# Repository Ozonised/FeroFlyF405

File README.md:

# FeroFlyF405

FeroFlyF405 is an opensource flight controller based on STM32F405 and runs the open source flight controller firmware, [INAV](https://github.com/iNavFlight/inav).

FeroFlyF405 is designed to be an open hardware platform that enthusiasts and developers can study, modify, build, and use in their own projects.

For those interested in the design process, watch the [YouTube](https://youtu.be/mWAzVRxgooY) video.

## Features

* **Microcontroller:** STM32F405
* **IMU:** LSM6DSL 6-axis accelerometer and gyroscope
* **Barometer:** DPS368
* **Firmware:** INAV
* **Motor outputs:** 12 timer-based output channels
* **CAN bus:** For compatible peripherals
* **I2C:** External sensor and peripheral connectivity
* **UARTs:** 3 serial ports
* **PINIO:** 2 programmable GPIO outputs
* **Current sensing:** Dedicated input for an external current sensor

## Sponsor

A special thanks to **[NextPCB](https://www.nextpcb.com/?code=ozonised)** for sponsoring the FeroFlyF405 project and supporting the development of this open-source flight controller.

Their support helped bring the custom PCB design from the screen to the physical board.

Get high quality PCBs for your project at an affordable rate from **[NextPCB](https://www.nextpcb.com/)**.

## Download
Grab the gerbers and kicad file for the latest stable version from the **[release](https://github.com/Ozonised/FeroFlyF405/releases)** tab.

## Connectivity

| Interface      | Quantity | Purpose                                             |
| -------------- | -------: | --------------------------------------------------- |
| Motor outputs  |       12 | ESCs and other compatible timer-based outputs       |
| CAN bus        |        1 | Compatible CAN peripherals                          |
| I2C            |        1 | External sensors and peripherals                    |
| UART           |        3 | Receivers, GPS, telemetry, and other serial devices |
| PINIO          |        2 | User-configurable GPIO outputs                      |
| Current sensor |        1 | External current-sensing module                     |

> **Note:** Motor output capabilities depend on timer allocation, DMA availability, and firmware configuration. Not all outputs necessarily support every ESC protocol.

## Connectors and Pinout

FeroFlyF405 follows the **Pixhawk connector and pinout standard** for its applicable peripheral interfaces and uses **JST-GH series connectors**.

The PINIO and current-sensor connectors are exceptions to this convention.

## Firmware

FeroFlyF405 runs [INAV](https://github.com/iNavFlight/inav), an open-source flight control firmware for multirotor, fixed-wing, and other UAV platforms.

FeroFlyF405 uses a board-specific INAV target to configure its MCU pins, sensors, timers, communication interfaces, and other hardware resources.

Useful links:
* [FeroFlyF405 Target & Binary](https://github.com/Ozonised/FeroFlyF405-INAV-files)
* [INAV source code](https://github.com/iNavFlight/inav)
* [INAV documentation](https://inavflight.github.io/)

## 3D-Printed Enclosure

The FeroFlyF405 enclosure consists of three 3D-printable parts:

* **Enclosure Top** (`FeroFlyF405 Enclosure-Top.stl`) — Upper section of the enclosure.
* **Enclosure Bottom** (`FeroFlyF405 Enclosure-Bottom.stl`) — Lower section of the enclosure.
* **LED Cap** (`FeroFlyF405 Enclosure-Led Cap.stl`) — Cover for the status and power LEDs, designed to be printed using translucent filament to allow the LED light to pass through.

### Printing Recommendations

* **Top and Bottom:** PETG filament is recommended for durability and heat resistance.
* **LED Cap:** Use translucent filament for better LED visibility.
* **Fasteners:** The enclosure uses M3 screws and threaded inserts.

The STL files are provided so you can print and assemble the enclosure yourself.

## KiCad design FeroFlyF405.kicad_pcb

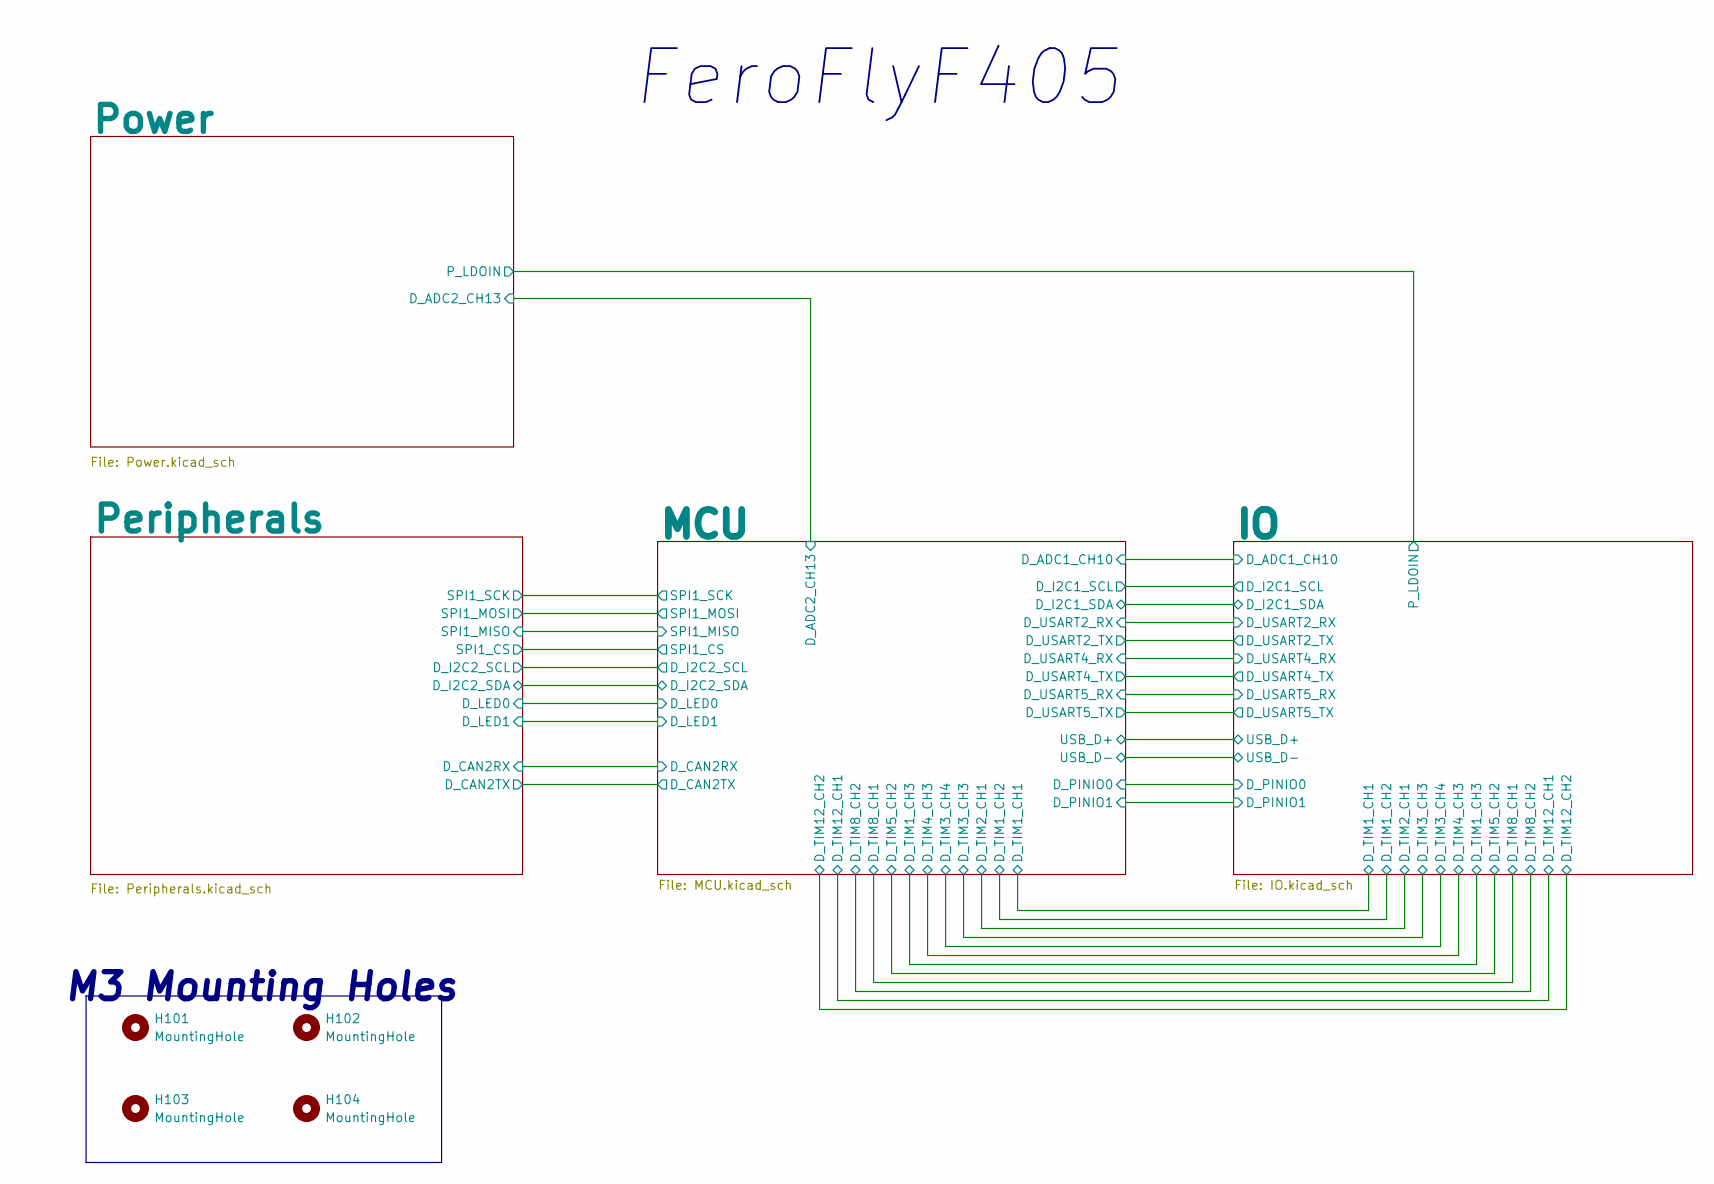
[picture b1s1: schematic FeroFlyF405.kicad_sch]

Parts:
H101, H102, H103, H104: MountingHole; MountingHole_3.2mm_M3

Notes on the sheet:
M3 Mounting Holes
FeroFlyF405

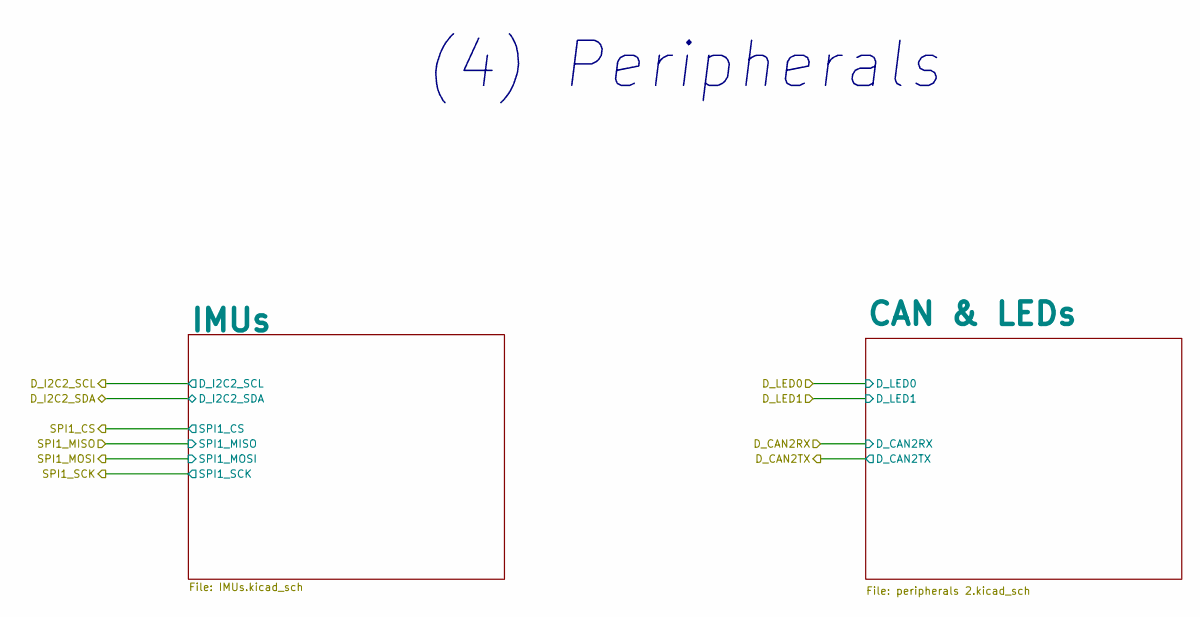
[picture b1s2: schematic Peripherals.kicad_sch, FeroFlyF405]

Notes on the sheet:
(4) Peripherals

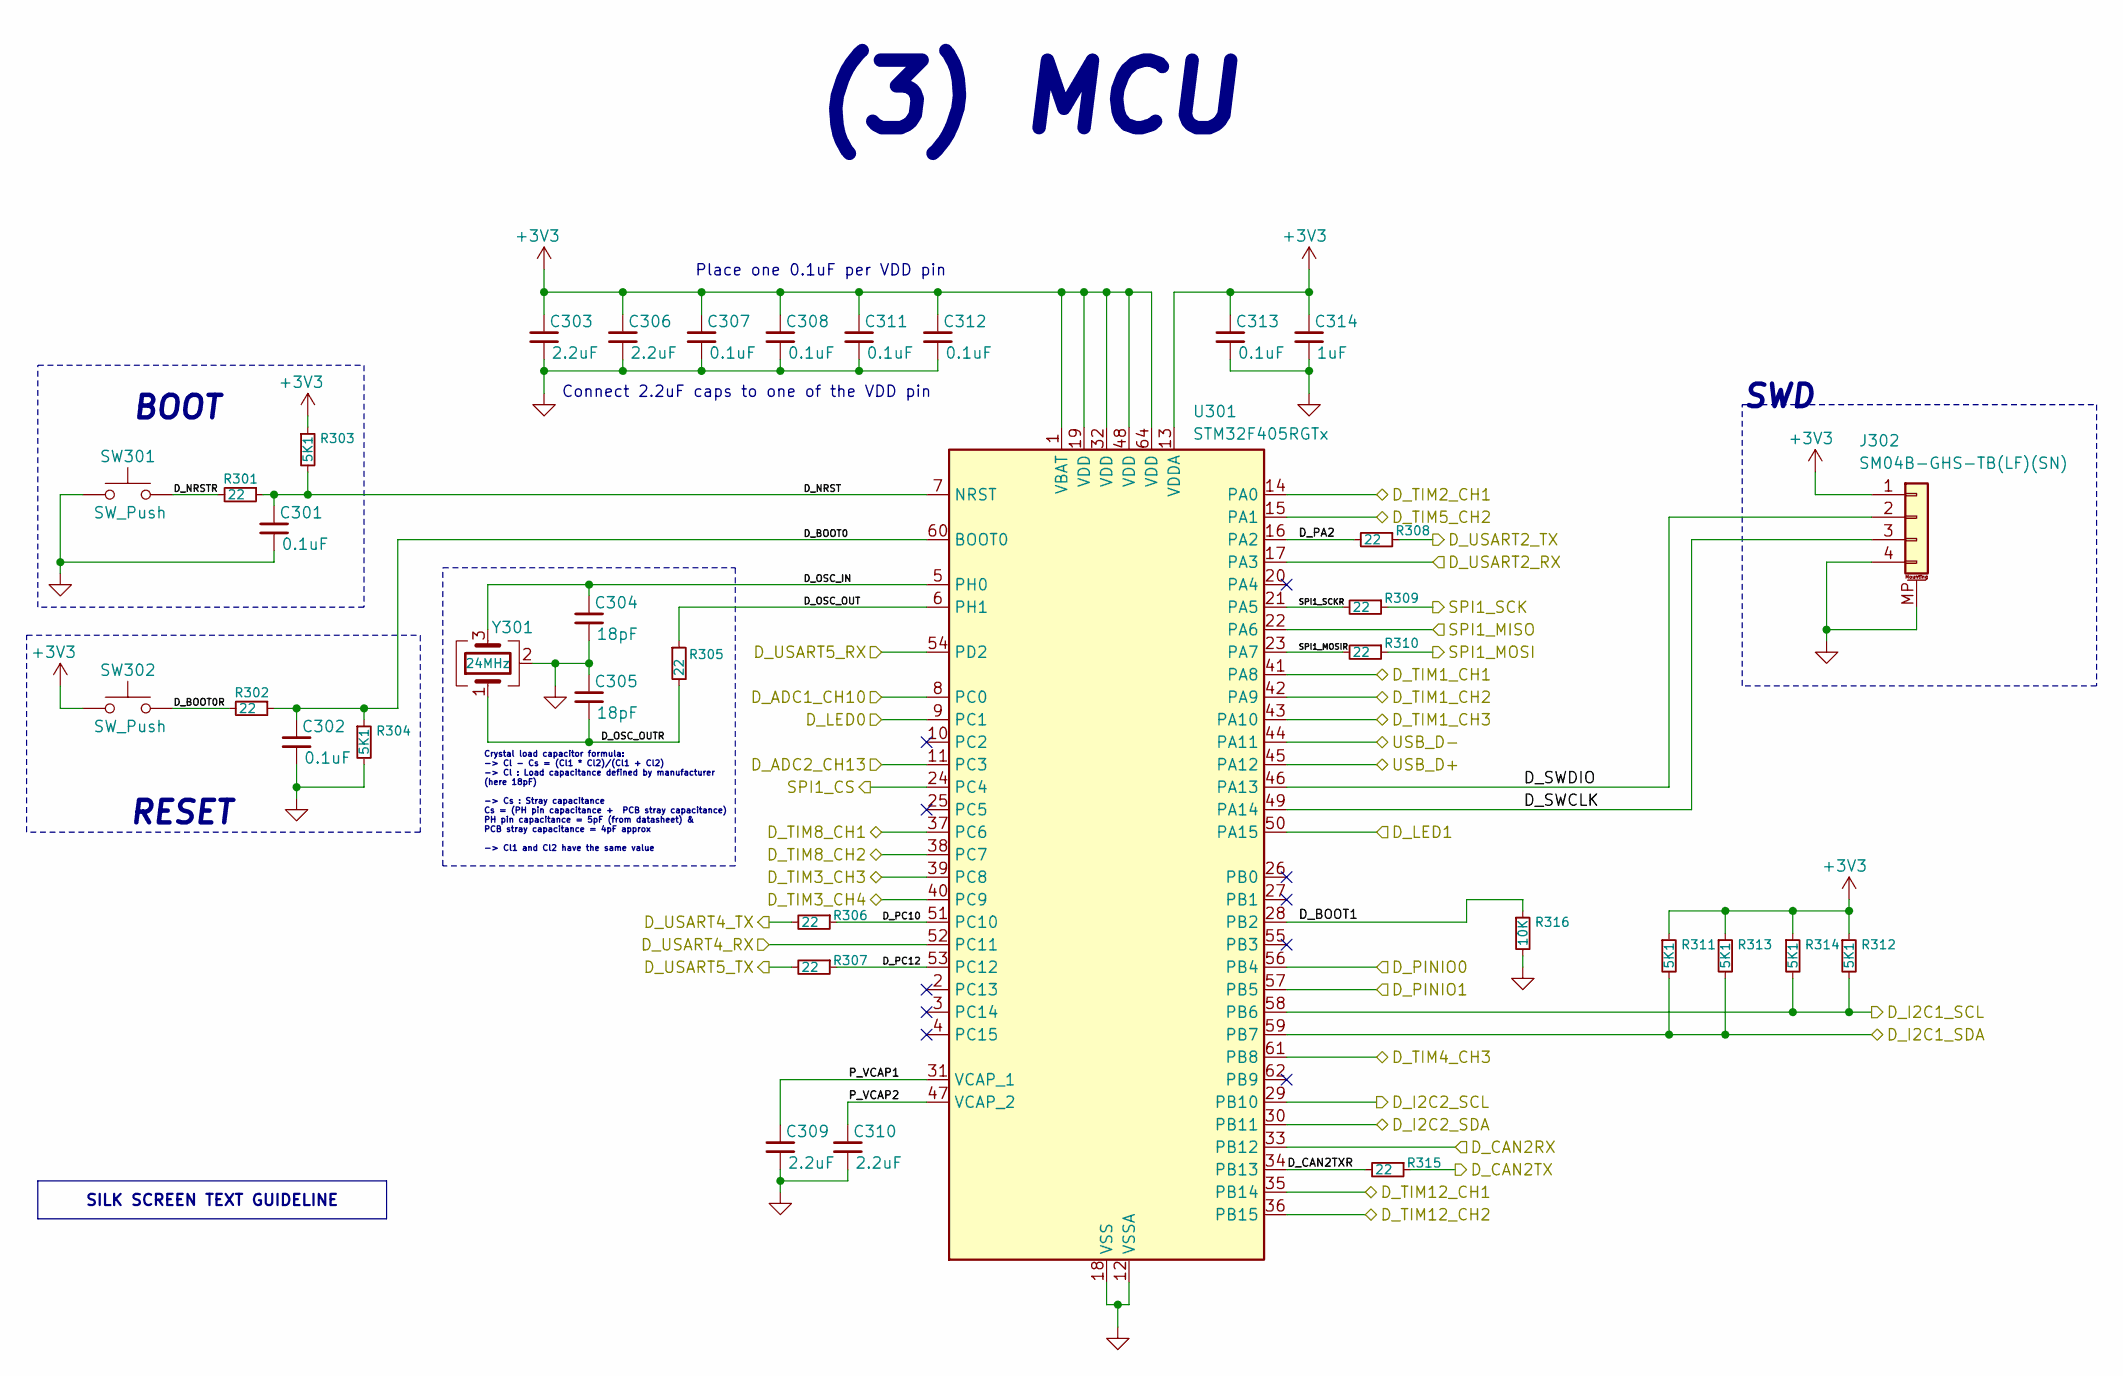
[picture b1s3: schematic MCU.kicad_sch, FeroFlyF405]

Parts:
C301, C302, C307, C308, C311, C312, C313: 0.1uF; C_0603_1608Metric_Pad1.08x0.95mm_HandSolder; MPN C1608X5R1H104K080AA
C303, C306, C309, C310: 2.2uF; C_0805_2012Metric_Pad1.18x1.45mm_HandSolder; MPN GCM21BR71C225KA64L
C304, C305: 18pF; C_0603_1608Metric_Pad1.08x0.95mm_HandSolder; MPN 06035A180JAT4A
C314: 1uF; C_0603_1608Metric_Pad1.08x0.95mm_HandSolder; MPN C1608X7R1V105K080AC
J302: SM04B-GHS-TB(LF)(SN); JST_GH_SM04B-GHS-TB_1x04-1MP_P1.25mm_Horizontal; MPN SM04B-GHS-TB(LF)(SN)
R301, R302, R305, R306, R307, R308, R309, R310, R315: 22; C_0603_1608Metric_Pad1.08x0.95mm_HandSolder; MPN CR0603-FX-22R0ELF
R303, R304, R311, R312, R313, R314: 5K1; R_0603_1608Metric_Pad0.98x0.95mm_HandSolder; MPN CR0603-FX-5101ELF
R316: 10K; R_0603_1608Metric_Pad0.98x0.95mm_HandSolder; MPN CR0603-FX-1002ELF
SW301, SW302: SW_Push; SW_Push_1P1T_NO_CK_KMR2; MPN RKB2SJM250SMTR LFS
U301: STM32F405RGTx; LQFP-64_10x10mm_P0.5mm; MPN STM32F405RGT6
Y301: 24MHz; Crystal_SMD_3225-4Pin_3.2x2.5mm; MPN ABM8-24.000MHZ-D4Y-T

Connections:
+3V3: C303.1, C306.1, C307.1, C308.1, C311.1, C312.1, C313.1, C314.1, J302.1, R303.1, R311.1, R312.1, R313.1, R314.1, SW302.1, U301.1 (VBAT), U301.13 (VDDA), U301.19 (VDD), U301.32 (VDD), U301.48 (VDD), U301.64 (VDD); also elsewhere on the board
/IO/D_ADC1_CH10: U301.8 (PC0); also elsewhere on the board
/IO/D_I2C1_SCL: R312.2, R314.2, U301.58 (PB6); also elsewhere on the board
/IO/D_I2C1_SDA: R311.2, R313.2, U301.59 (PB7); also elsewhere on the board
/IO/D_PINIO0: U301.56 (PB4); also elsewhere on the board
/IO/D_PINIO1: U301.57 (PB5); also elsewhere on the board
/IO/D_TIM1_CH1: U301.41 (PA8); also elsewhere on the board
/IO/D_TIM1_CH2: U301.42 (PA9); also elsewhere on the board
/IO/D_TIM1_CH3: U301.43 (PA10); also elsewhere on the board
/IO/D_TIM2_CH1: U301.14 (PA0); also elsewhere on the board
/IO/D_TIM3_CH3: U301.39 (PC8); also elsewhere on the board
/IO/D_TIM3_CH4: U301.40 (PC9); also elsewhere on the board
/IO/D_TIM4_CH3: U301.61 (PB8); also elsewhere on the board
/IO/D_TIM5_CH2: U301.15 (PA1); also elsewhere on the board
/IO/D_TIM8_CH1: U301.37 (PC6); also elsewhere on the board
/IO/D_TIM8_CH2: U301.38 (PC7); also elsewhere on the board
/IO/D_TIM12_CH1: U301.35 (PB14); also elsewhere on the board
/IO/D_TIM12_CH2: U301.36 (PB15); also elsewhere on the board
/IO/D_USART2_RX: U301.17 (PA3); also elsewhere on the board
/IO/D_USART2_TX: R308.1; also elsewhere on the board
/IO/D_USART4_RX: U301.52 (PC11); also elsewhere on the board
/IO/D_USART4_TX: R306.2; also elsewhere on the board
/IO/D_USART5_RX: U301.54 (PD2); also elsewhere on the board
/IO/D_USART5_TX: R307.2; also elsewhere on the board
/IO/USB_D+: U301.45 (PA12); also elsewhere on the board
/IO/USB_D-: U301.44 (PA11); also elsewhere on the board
/MCU/D_ADC2_CH13: U301.11 (PC3); also elsewhere on the board
/MCU/D_BOOT0: C302.1, R302.1, R304.1, U301.60 (BOOT0)
/MCU/D_BOOT0R: R302.2, SW302.2
/MCU/D_BOOT1: R316.1, U301.28 (PB2)
/MCU/D_CAN2RX: U301.33 (PB12); also elsewhere on the board
/MCU/D_CAN2TX: R315.1; also elsewhere on the board
/MCU/D_CAN2TXR: R315.2, U301.34 (PB13)
/MCU/D_I2C2_SCL: U301.29 (PB10); also elsewhere on the board
/MCU/D_I2C2_SDA: U301.30 (PB11); also elsewhere on the board
/MCU/D_LED0: U301.9 (PC1); also elsewhere on the board
/MCU/D_LED1: U301.50 (PA15); also elsewhere on the board
/MCU/D_NRST: C301.1, R301.1, R303.2, U301.7 (NRST)
/MCU/D_NRSTR: R301.2, SW301.2
/MCU/D_OSC_IN: C304.1, U301.5 (PH0), Y301.3
/MCU/D_OSC_OUT: R305.1, U301.6 (PH1)
/MCU/D_OSC_OUTR: C305.2, R305.2, Y301.1
/MCU/D_PA2: R308.2, U301.16 (PA2)
/MCU/D_PC10: R306.1, U301.51 (PC10)
/MCU/D_PC12: R307.1, U301.53 (PC12)
/MCU/D_SWCLK: J302.3, U301.49 (PA14)
/MCU/D_SWDIO: J302.2, U301.46 (PA13)
/MCU/P_VCAP1: C309.1, U301.31 (VCAP_1)
/MCU/P_VCAP2: C310.1, U301.47 (VCAP_2)
/MCU/SPI1_CS: U301.24 (PC4); also elsewhere on the board
/MCU/SPI1_MISO: U301.22 (PA6); also elsewhere on the board
/MCU/SPI1_MOSI: R310.1; also elsewhere on the board
/MCU/SPI1_MOSIR: R310.2, U301.23 (PA7)
/MCU/SPI1_SCK: R309.1; also elsewhere on the board
/MCU/SPI1_SCKR: R309.2, U301.21 (PA5)
GND: C301.2, C302.2, C303.2, C304.2, C305.1, C306.2, C307.2, C308.2, C309.2, C310.2, C311.2, C312.2, C313.2, C314.2, J302.4, J302.MP (MountPin), R304.2, R316.2, SW301.1, U301.12 (VSSA), U301.18 (VSS), U301.63 (VSS), Y301.2 (G), Y301.4 (G); also elsewhere on the board

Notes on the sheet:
RESET
SWD
Place one 0.1uF per VDD pin
Crystal load capacitor formula: -> Cl - Cs = (Cl1 * Cl2)/(Cl1 + Cl2) -> Cl : Load capacitance defined by manufacturer (here 18pF) -> Cs : Stray capacitance Cs = (PH pin capacitance + PCB stray capacitance) PH pin capacitance = 5pF (from datasheet) & PCB stray capacitance = 4pF approx -> Cl1 and Cl2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
(3) MCU
Connect 2.2uF caps to one of the VDD pin
BOOT
SILK SCREEN TEXT GUIDELINE

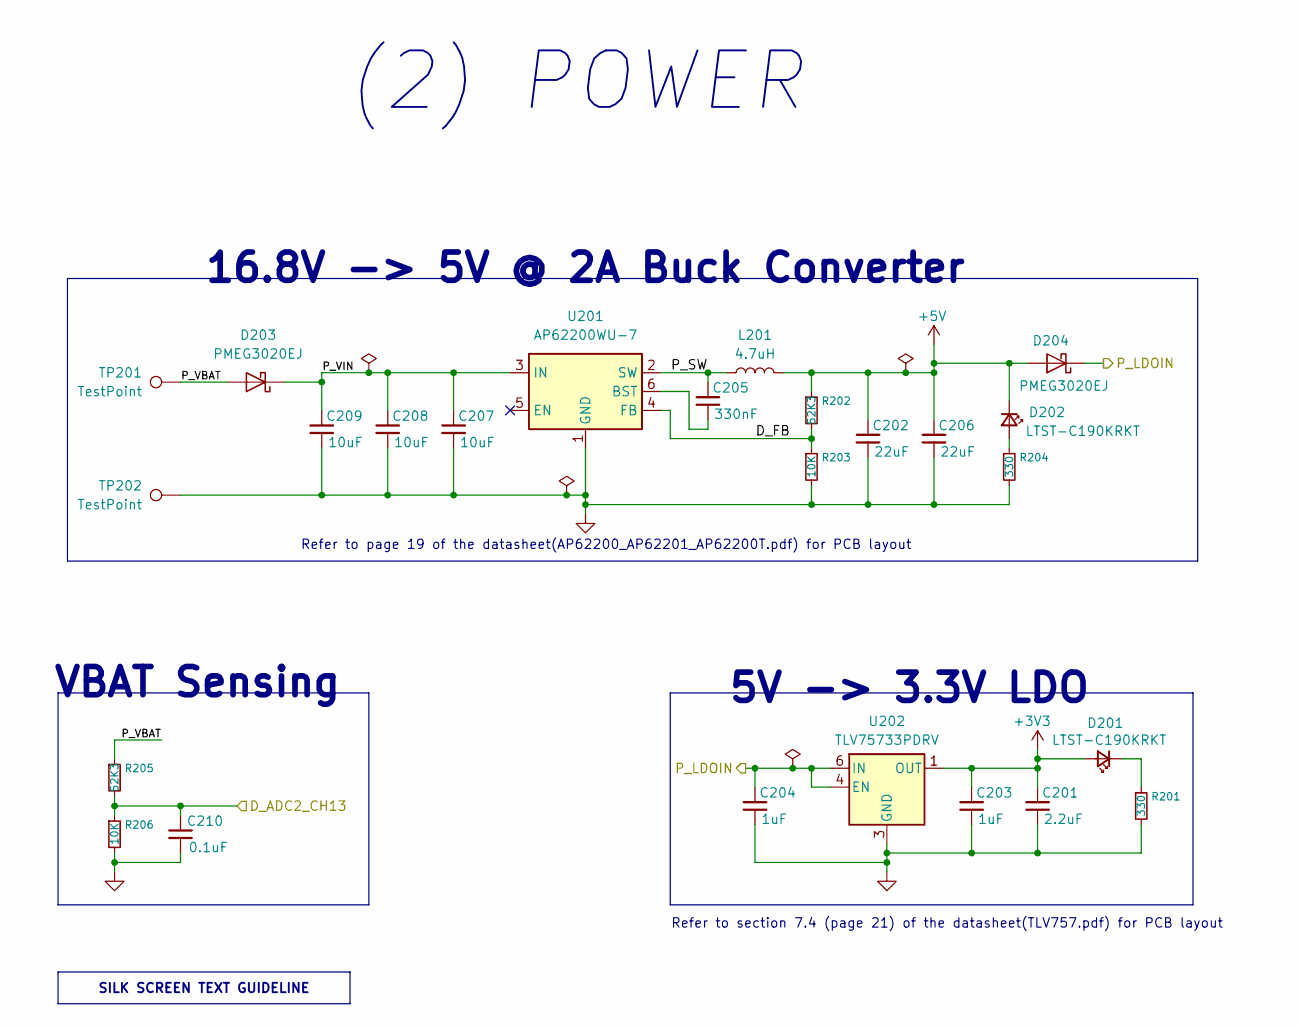
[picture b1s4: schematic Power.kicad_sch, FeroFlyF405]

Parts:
C201: 2.2uF; C_0805_2012Metric_Pad1.18x1.45mm_HandSolder; MPN GCM21BR71C225KA64L
C202, C206: 22uF; C_1210_3225Metric_Pad1.33x2.70mm_HandSolder; MPN C3225X5R1C226M250AA
C203, C204: 1uF; C_0603_1608Metric_Pad1.08x0.95mm_HandSolder; MPN C1608X7R1V105K080AC
C205: 330nF; C_0805_2012Metric_Pad1.18x1.45mm_HandSolder; MPN CGA4J2X7R1H334K125AA
C207, C208, C209: 10uF; C_1206_3216Metric_Pad1.33x1.80mm_HandSolder; MPN C3216X5R1E106K160AB
C210: 0.1uF; C_0603_1608Metric_Pad1.08x0.95mm_HandSolder; MPN C1608X5R1H104K080AA
D201, D202: LTST-C190KRKT; LED_0603_1608Metric_Pad1.05x0.95mm_HandSolder; MPN LTST-C190KRKT
D203, D204: PMEG3020EJ; D_SOD-323F; MPN PMEG3020EJ,115
L201: 4.7uH; L_Abracon_ASPI-4030S; MPN ASPI-4030S-4R7M-T
R201, R204: 330; R_0603_1608Metric_Pad0.98x0.95mm_HandSolder; MPN CR0603-FX-3300ELF
R202, R205: 52K3; C_0603_1608Metric_Pad1.08x0.95mm_HandSolder; MPN CR0603-FX-5232ELF
R203, R206: 10K; R_0603_1608Metric_Pad0.98x0.95mm_HandSolder; MPN CR0603-FX-1002ELF
TP201, TP202: TestPoint; TestPoint_Pad_2.0x2.0mm
U201: AP62200WU-7; TSOT-23-6; MPN AP62200WU-7
U202: TLV75733PDRV; WSON-6-1EP_2x2mm_P0.65mm_EP1x1.6mm; MPN TLV75733PDRVR

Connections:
+3V3: C201.1, C203.1, D201.2 (A), U202.1 (OUT); also elsewhere on the board
+5V: C202.1, C206.1, D202.1 (K), D204.2 (A), L201.2, R202.1; also elsewhere on the board
/IO/P_LDOIN: C204.1, D204.1 (K), U202.4 (EN), U202.6 (IN); also elsewhere on the board
/MCU/D_ADC2_CH13: C210.1, R205.2, R206.1; also elsewhere on the board
/Power/D_FB: R202.2, R203.1, U201.4 (FB)
/Power/P_SW: C205.1, L201.1, U201.2 (SW)
/Power/P_VBAT: D203.2 (A), R205.1, TP201.1 (1_1)
/Power/P_VIN: C207.1, C208.1, C209.1, D203.1 (K), U201.3 (IN)
GND: C201.2, C202.2, C203.2, C204.2, C206.2, C207.2, C208.2, C209.2, C210.2, R201.2, R203.2, R204.2, R206.2, TP202.1 (1_1), U201.1 (GND), U202.3 (GND), U202.7 (GND); also elsewhere on the board
unnamed: D201.1 (K), R201.1
unnamed: D202.2 (A), R204.1
unnamed: C205.2, U201.6 (BST)

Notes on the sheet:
Refer to page 19 of the datasheet(AP62200_AP62201_AP62200T.pdf) for PCB layout
5V -> 3.3V LDO
16.8V -> 5V @ 2A Buck Converter
(2) POWER
Refer to section 7.4 (page 21) of the datasheet(TLV757.pdf) for PCB layout
VBAT Sensing
SILK SCREEN TEXT GUIDELINE

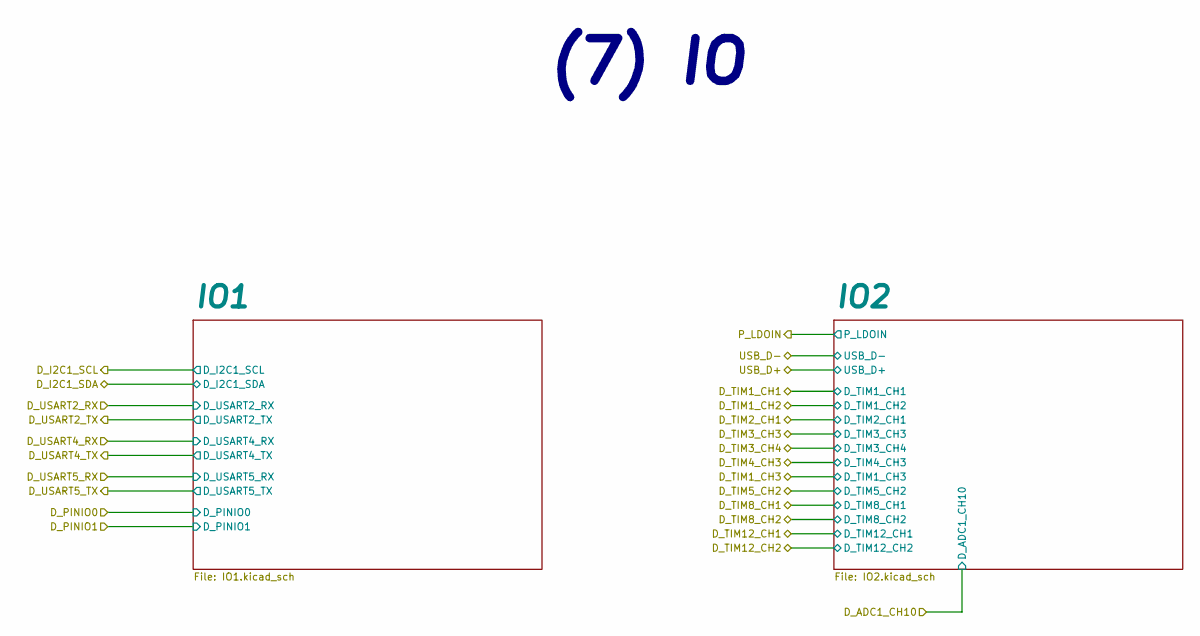
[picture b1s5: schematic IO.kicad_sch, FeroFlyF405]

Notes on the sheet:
(7) IO

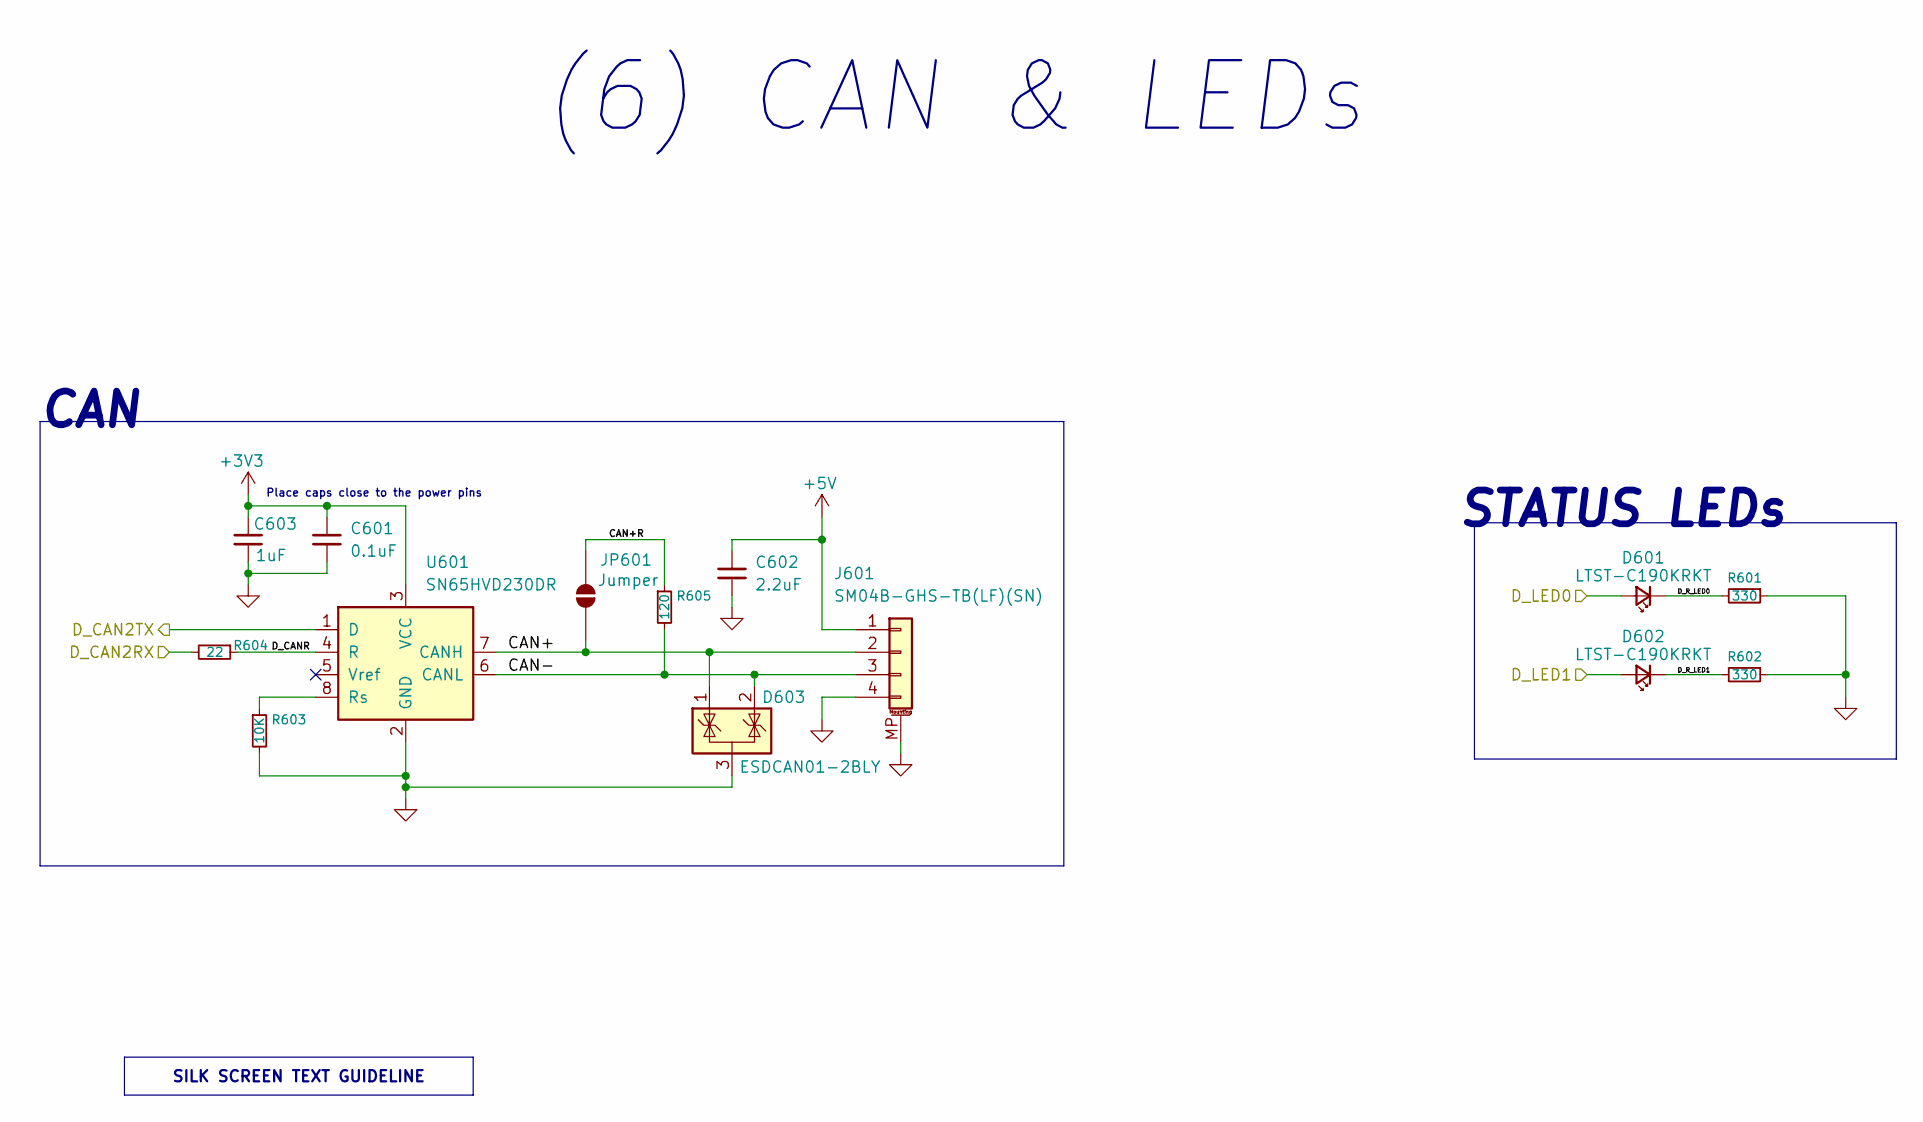
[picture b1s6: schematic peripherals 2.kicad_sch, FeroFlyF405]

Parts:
C601: 0.1uF; C_0603_1608Metric_Pad1.08x0.95mm_HandSolder; MPN C1608X5R1H104K080AA
C602: 2.2uF; C_0805_2012Metric_Pad1.18x1.45mm_HandSolder; MPN GCM21BR71C225KA64L
C603: 1uF; C_0603_1608Metric_Pad1.08x0.95mm_HandSolder; MPN C1608X7R1V105K080AC
D601, D602: LTST-C190KRKT; LED_0603_1608Metric_Pad1.05x0.95mm_HandSolder; MPN LTST-C190KRKT
D603: ESDCAN01-2BLY; SOT-23; MPN ESDCAN01-2BLY
J601: SM04B-GHS-TB(LF)(SN); JST_GH_SM04B-GHS-TB_1x04-1MP_P1.25mm_Horizontal; MPN SM04B-GHS-TB(LF)(SN)
JP601: Jumper; SolderJumper-2_P1.3mm_Open_TrianglePad1.0x1.5mm
R601, R602: 330; R_0603_1608Metric_Pad0.98x0.95mm_HandSolder; MPN CR0603-FX-3300ELF
R603: 10K; R_0603_1608Metric_Pad0.98x0.95mm_HandSolder; MPN CR0603-FX-1002ELF
R604: 22; C_0603_1608Metric_Pad1.08x0.95mm_HandSolder; MPN CR0603-FX-22R0ELF
R605: 120; R_1206_3216Metric_Pad1.30x1.75mm_HandSolder; MPN CR1206-FX-1200ELF
U601: SN65HVD230DR; SOIC-8_3.9x4.9mm_P1.27mm; MPN SN65HVD230DR

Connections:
+3V3: C601.1, C603.1, U601.3 (VCC); also elsewhere on the board
+5V: C602.1, J601.1; also elsewhere on the board
/MCU/D_CAN2RX: R604.2; also elsewhere on the board
/MCU/D_CAN2TX: U601.1 (D); also elsewhere on the board
/MCU/D_LED0: D601.2 (A); also elsewhere on the board
/MCU/D_LED1: D602.2 (A); also elsewhere on the board
/Peripherals/CAN & LEDs/CAN+: D603.1 (K), J601.2, JP601.1 (A), U601.7 (CANH)
/Peripherals/CAN & LEDs/CAN+R: JP601.2 (B), R605.1
/Peripherals/CAN & LEDs/CAN-: D603.2 (K), J601.3, R605.2, U601.6 (CANL)
/Peripherals/CAN & LEDs/D_CANR: R604.1, U601.4 (R)
/Peripherals/CAN & LEDs/D_R_LED0: D601.1 (K), R601.2
/Peripherals/CAN & LEDs/D_R_LED1: D602.1 (K), R602.2
GND: C601.2, C602.2, C603.2, D603.3 (A), J601.4, J601.MP (MountPin), R601.1, R602.1, R603.2, U601.2 (GND); also elsewhere on the board
unnamed: R603.1, U601.8 (Rs)

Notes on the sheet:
(6) CAN & LEDs
STATUS LEDs
Place caps close to the power pins
CAN
SILK SCREEN TEXT GUIDELINE

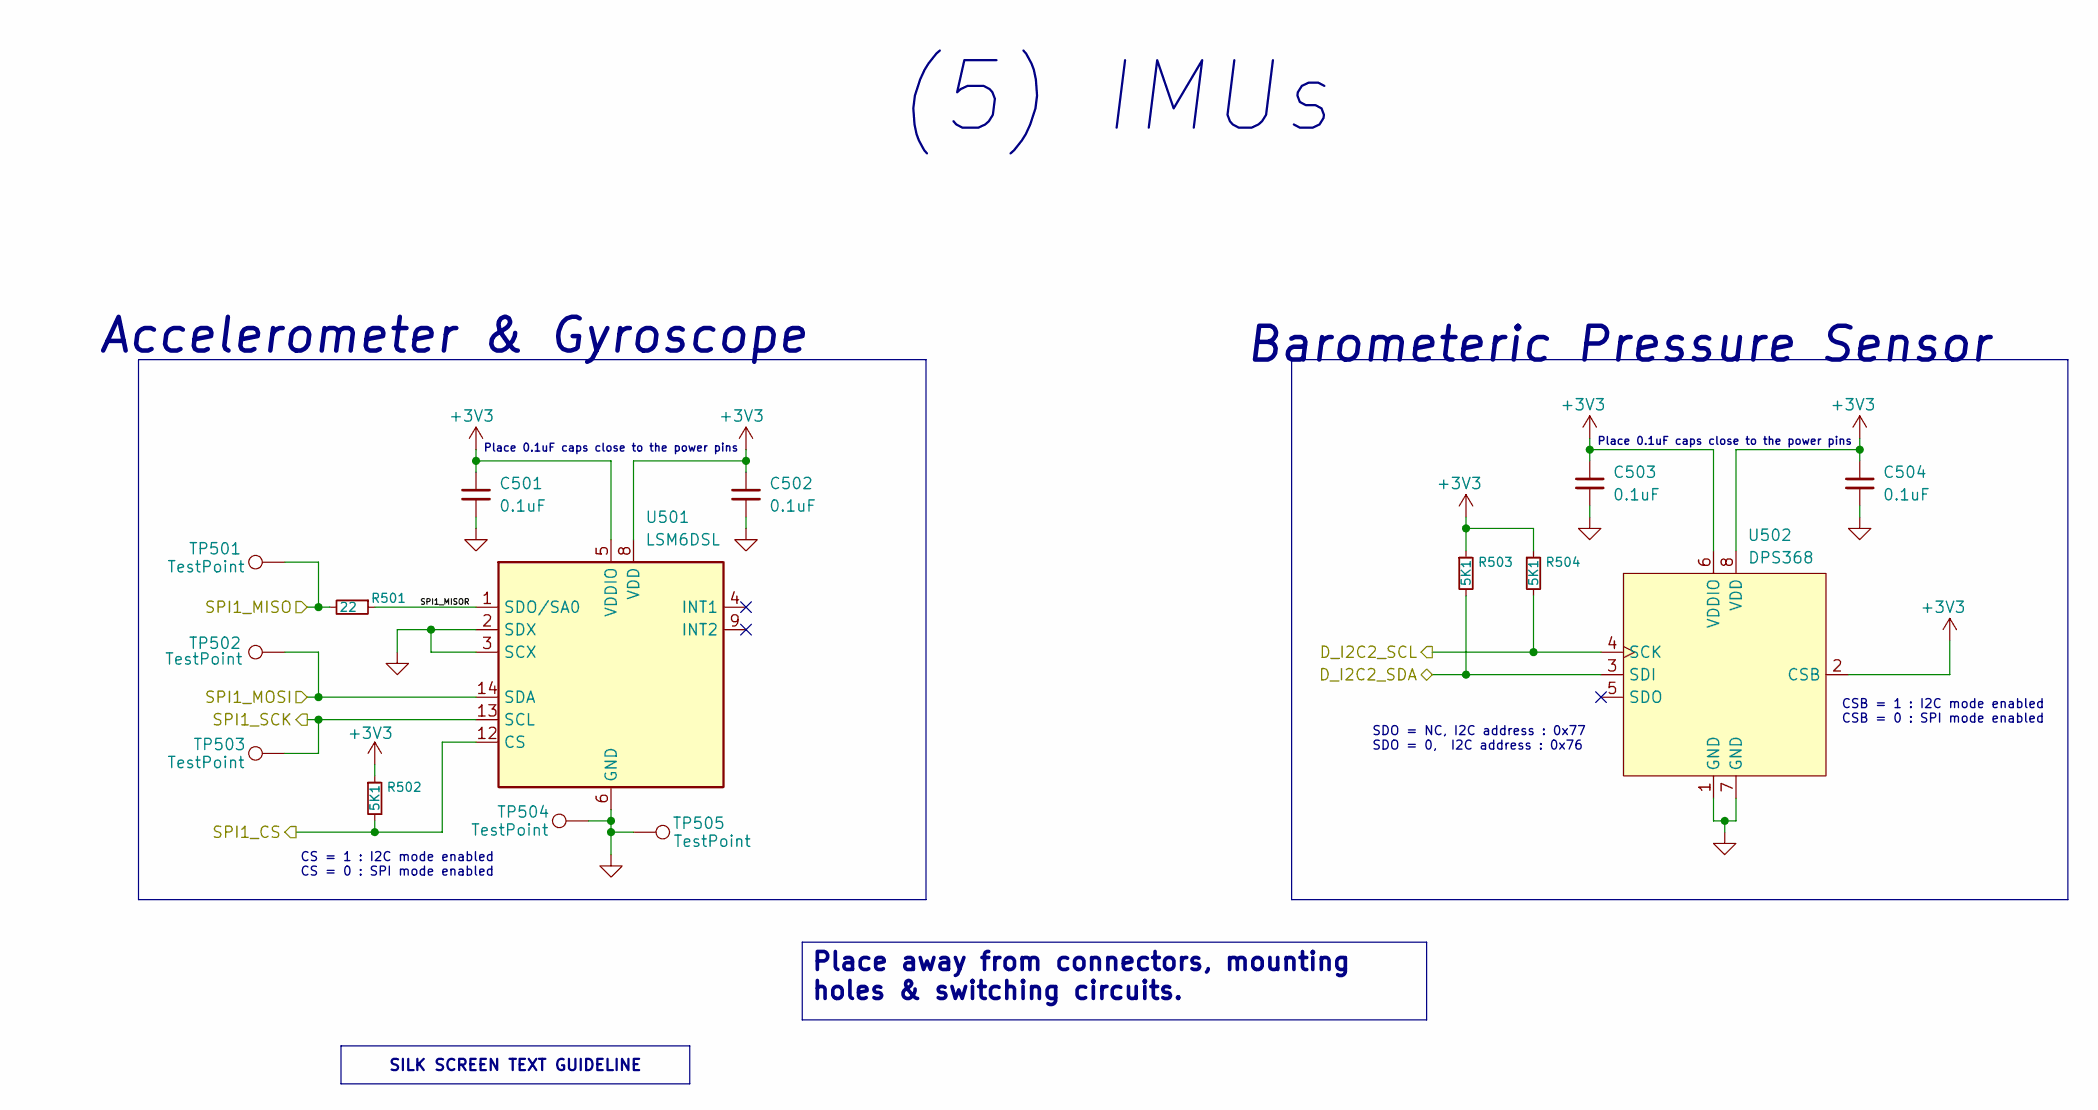
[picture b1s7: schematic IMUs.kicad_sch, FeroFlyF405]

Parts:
C501, C502, C503, C504: 0.1uF; C_0603_1608Metric_Pad1.08x0.95mm_HandSolder; MPN C1608X5R1H104K080AA
R501: 22; C_0603_1608Metric_Pad1.08x0.95mm_HandSolder; MPN CR0603-FX-22R0ELF
R502, R503, R504: 5K1; R_0603_1608Metric_Pad0.98x0.95mm_HandSolder; MPN CR0603-FX-5101ELF
TP501, TP502, TP503, TP504, TP505: TestPoint; TestPoint_Pad_D1.0mm
U501: LSM6DSL; LGA-14_3x2.5mm_P0.5mm_LayoutBorder3x4y; MPN LSM6DSL
U502: DPS368; Bosch_LGA-8_2x2.5mm_P0.65mm_ClockwisePinNumbering

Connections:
+3V3: C501.1, C502.1, C503.1, C504.1, R502.1, R503.1, R504.1, U501.5 (VDDIO), U501.8 (VDD), U502.2 (CSB), U502.6 (VDDIO), U502.8 (VDD); also elsewhere on the board
/MCU/D_I2C2_SCL: R504.2, U502.4 (SCK); also elsewhere on the board
/MCU/D_I2C2_SDA: R503.2, U502.3 (SDI); also elsewhere on the board
/MCU/SPI1_CS: R502.2, U501.12 (CS); also elsewhere on the board
/MCU/SPI1_MISO: R501.2, TP501.1 (1_1); also elsewhere on the board
/MCU/SPI1_MOSI: TP502.1 (1_1), U501.14 (SDA); also elsewhere on the board
/MCU/SPI1_SCK: TP503.1 (1_1), U501.13 (SCL); also elsewhere on the board
/Peripherals/IMUs/SPI1_MISOR: R501.1, U501.1 (SDO/SA0)
GND: C501.2, C502.2, C503.2, C504.2, TP504.1 (1_1), TP505.1 (1_1), U501.2 (SDX), U501.3 (SCX), U501.6 (GND), U501.7 (GND), U502.1 (GND), U502.7 (GND); also elsewhere on the board

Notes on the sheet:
SDO = NC, I2C address : 0x77 SDO = 0, I2C address : 0x76
CSB = 1 : I2C mode enabled CSB = 0 : SPI mode enabled
Accelerometer & Gyroscope
(5) IMUs
CS = 1 : I2C mode enabled CS = 0 : SPI mode enabled
Place 0.1uF caps close to the power pins
Barometeric Pressure Sensor
SILK SCREEN TEXT GUIDELINE
Place away from connectors, mounting holes & switching circuits.

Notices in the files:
FeroFlyF405.kicad_pcb:
LICENSE: CERN-OHL-S-2.0
